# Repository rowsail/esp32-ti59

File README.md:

# esp32-ti59
This is a work in progress - do not use while the readme says this!

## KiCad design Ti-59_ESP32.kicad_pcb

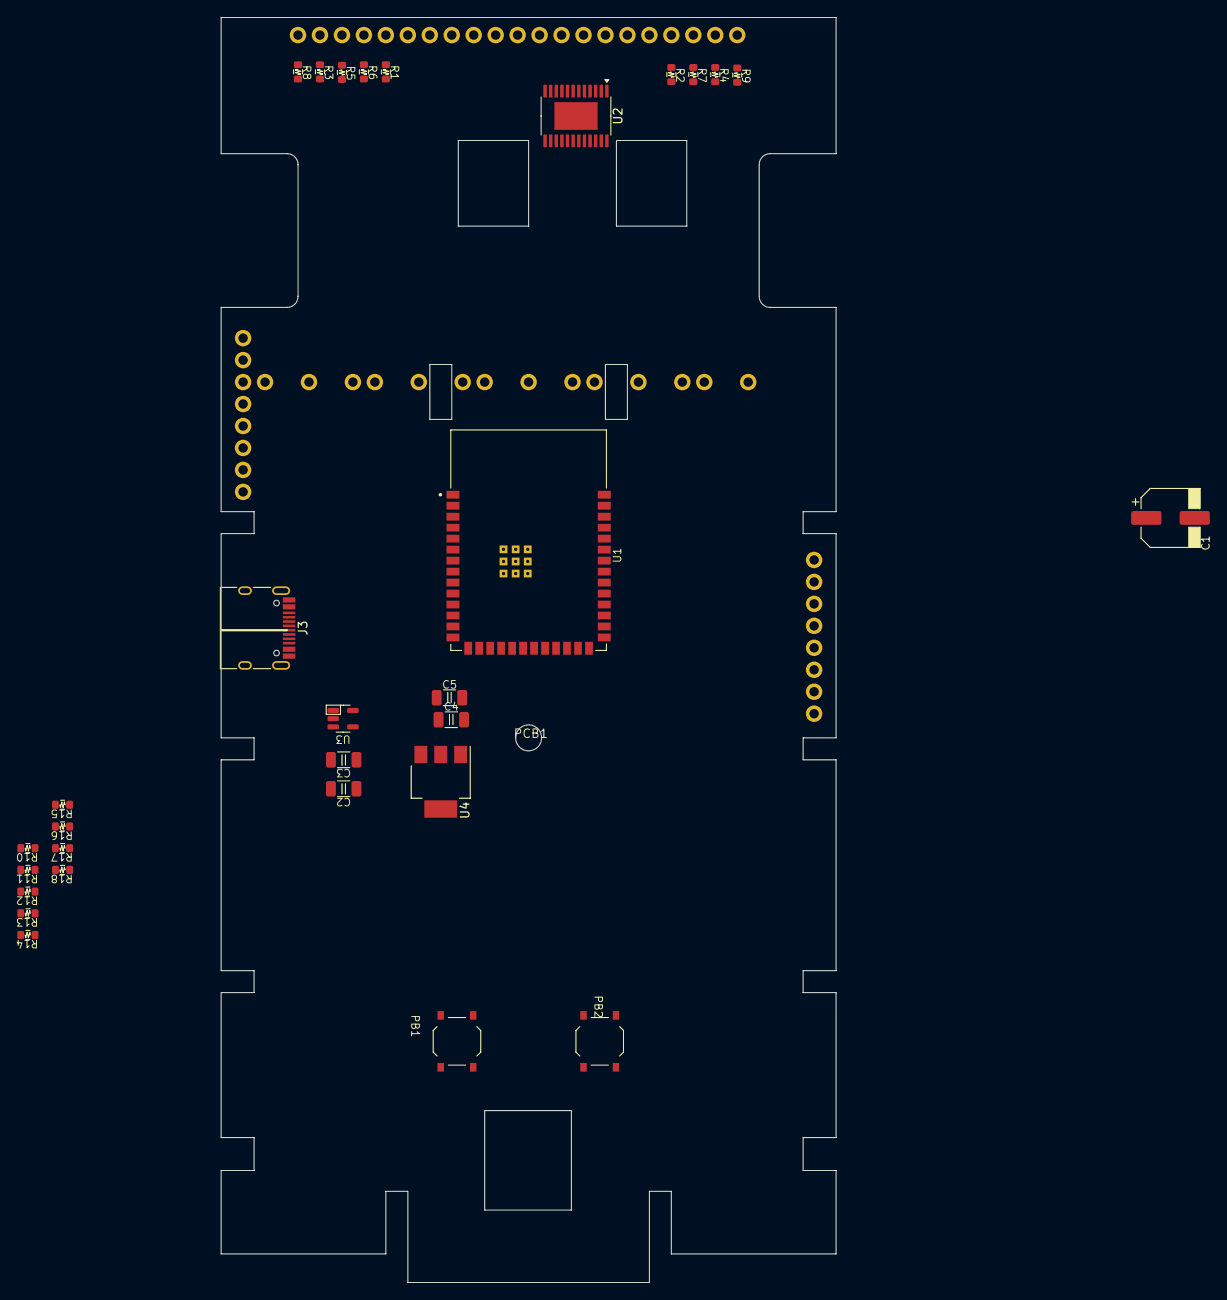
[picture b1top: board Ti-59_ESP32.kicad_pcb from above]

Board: 2 copper layers, 71.1 x 146.3 mm, 31 parts (0 on the bottom side), 50 nets, no tracks yet.

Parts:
C1: 56u 25V; CP_Elec_6.3x5.9
C2, C3, C4, C5: 10UF 50V 1206; C_1206_3216Metric
J3: HC-TYPE-C-16P-01A-R; USB_C_Receptacle_HRO_TYPE-C-31-M-12
PB1, PB2: TS-1187A-B-A-B
PCB1: TI-59-PCB; Ti59PCB
R1, R2, R3, R4, R5, R6, R7, R8, R9: 430R 0805; R_0603_1608Metric
R10, R11: 5K1 0603; R_0603_1608Metric
R12, R13: 4K7 0603; R_0603_1608Metric
R14, R15, R16, R17, R18: 10K 0603; R_0603_1608Metric
U1: ESP32-S3-WROOM-1U-N16R8; M ESP32 XCVR_ESP32-S3-WROOM-1-N4R2
U2: 74HC154PW,118; TSSOP-24-1EP_4.4x7.8mm_P0.65mm_EP3.2x5mm
U3: MCP73832T-2DCI/OT; SOT-23-5
U4: AMS1117-3.3; SOT-223-3_TabPin2

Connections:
3V3: C4.1, C5.1, R14.1, R15.1, R16.1, R17.1, R18.1, U1.2 (3V3), U2.24 (VCC), U4.2 (VO)
5V: C3.1, J3.A4 (VBUS), J3.A9 (VBUS), J3.B4 (VBUS), J3.B9 (VBUS), U3.4 (VDD(5V))
/KD: PCB1.KD, R14.2, U1.22 (IO14)
/KP: PCB1.KP, R15.2, U1.21 (IO13)
/KR: PCB1.KQ, R16.2, U1.18 (IO10)
/KS: PCB1.KS, R17.2, U1.17 (IO9)
/KT: PCB1.KT, R18.2, U1.12 (IO8)
GND: C1.2, C2.2, C3.2, C4.2, C5.2, J3.A1 (GND), J3.A12 (GND), J3.B1 (GND), J3.B12 (GND), PB1.2, PB2.2, R10.2, R11.2, R12.2, R13.2, U1.1 (GND), U1.40 (GND), U2.12 (GND), U3.2 (GND), U4.1 (GND)
unnamed: C1.1, C2.1, U3.3 (VBAT(4V2)), U4.3 (VI)
unnamed: J3.A5 (CC1), R10.1
unnamed: J3.B5 (CC2), R11.1
unnamed: PCB1.SA (A), R1.2
unnamed: PCB1.SB (B), R2.2
unnamed: PCB1.SC (C), R3.2
unnamed: PCB1.SD (D), R4.2
unnamed: PCB1.DPT (DP), R9.2
unnamed: PCB1.SE (E), R5.2
unnamed: PCB1.SF (F), R6.2
unnamed: PCB1.SG (G), R7.2
unnamed: PCB1.SH (H), R8.2
unnamed: PB1.1, U1.3 (EN)
unnamed: PB2.1, U1.27 (IO0/BOOT0)
unnamed: R1.1, U1.8 (IO15)
unnamed: R2.1, U1.9 (IO16)
unnamed: R3.1, U1.10 (IO17)
unnamed: R4.1, U1.11 (IO18)
unnamed: R5.1, U1.13 (IO19)
unnamed: R6.1, U1.14 (IO20)
unnamed: R7.1, U1.23 (IO21)
unnamed: R8.1, U1.28 (IO35)
unnamed: R9.1, U1.29 (IO36)
unnamed: U1.30 (IO37), U2.23 (A0)
unnamed: U1.31 (IO38), U2.22 (A1)
unnamed: U1.32 (IO39), U2.21 (A2)
unnamed: U1.33 (IO40), U2.20 (A3)
unnamed: J3.A6 (D+), J3.B6 (D+), U1.20 (USB_D+)
unnamed: J3.A7 (D-), J3.B7 (D-), U1.19 (USB_D-)
unnamed: PCB1.L12, U2.1 (S0)
unnamed: PCB1.L11, U2.2 (S1)
unnamed: PCB1.L10, U2.3 (S2)
unnamed: PCB1.D9, PCB1.L9, U2.4 (S3)
unnamed: PCB1.D8, PCB1.L8, U2.5 (S4)
unnamed: PCB1.D7, PCB1.L7, U2.6 (S5)
unnamed: PCB1.D6, PCB1.L6, U2.7 (S6)
unnamed: PCB1.D5, PCB1.L5, U2.8 (S7)
unnamed: PCB1.D4, PCB1.L4, U2.9 (S8)
unnamed: PCB1.D3, PCB1.L3, U2.10 (S9)
unnamed: PCB1.D2, PCB1.L2, U2.11 (S10)
unnamed: PCB1.D1, PCB1.L1, U2.13 (S11)
unnamed: R12.1, R13.1, U3.5 (PROG)
